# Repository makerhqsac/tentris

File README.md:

# tentris - Ten foot tall tetris game made from a boatload of neopixels

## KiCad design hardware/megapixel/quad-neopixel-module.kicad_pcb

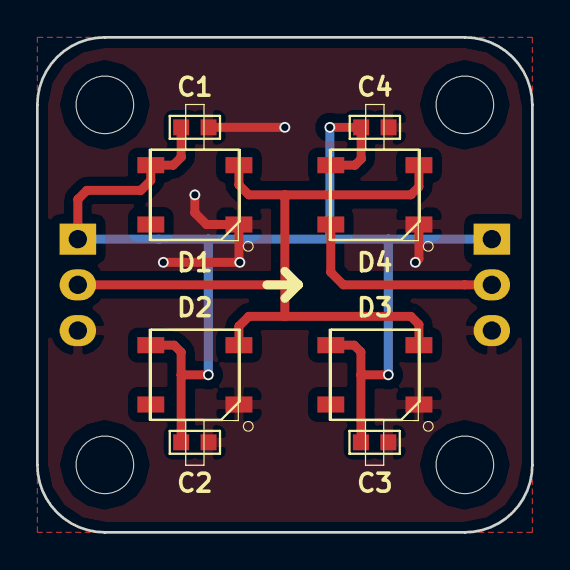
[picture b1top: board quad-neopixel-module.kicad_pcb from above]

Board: 2 copper layers, 27.5 x 27.5 mm, 10 parts (0 on the bottom side), 4 nets.

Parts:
C1, C2, C3, C4: CERAMIC-100NF-50V-10%-X7R_0603_; C0603
D1, D2, D3, D4: SMD-RGB-LED-4P; LED4-SMD-5050
P1, P2: CONN_01X03; Pin_Header_Straight_1x03

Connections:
DIN: D1.4, D2.4, D3.4, D4.4, P1.2
DOUT: D4.2, P2.2
GND: C1.2, C2.2, C3.2, C4.2, D1.3, D2.3, D3.3, D4.3, P1.3, P2.3
VCC: C1.1, C2.1, C3.1, C4.1, D1.1, D2.1, D3.1, D4.1, P1.1, P2.1

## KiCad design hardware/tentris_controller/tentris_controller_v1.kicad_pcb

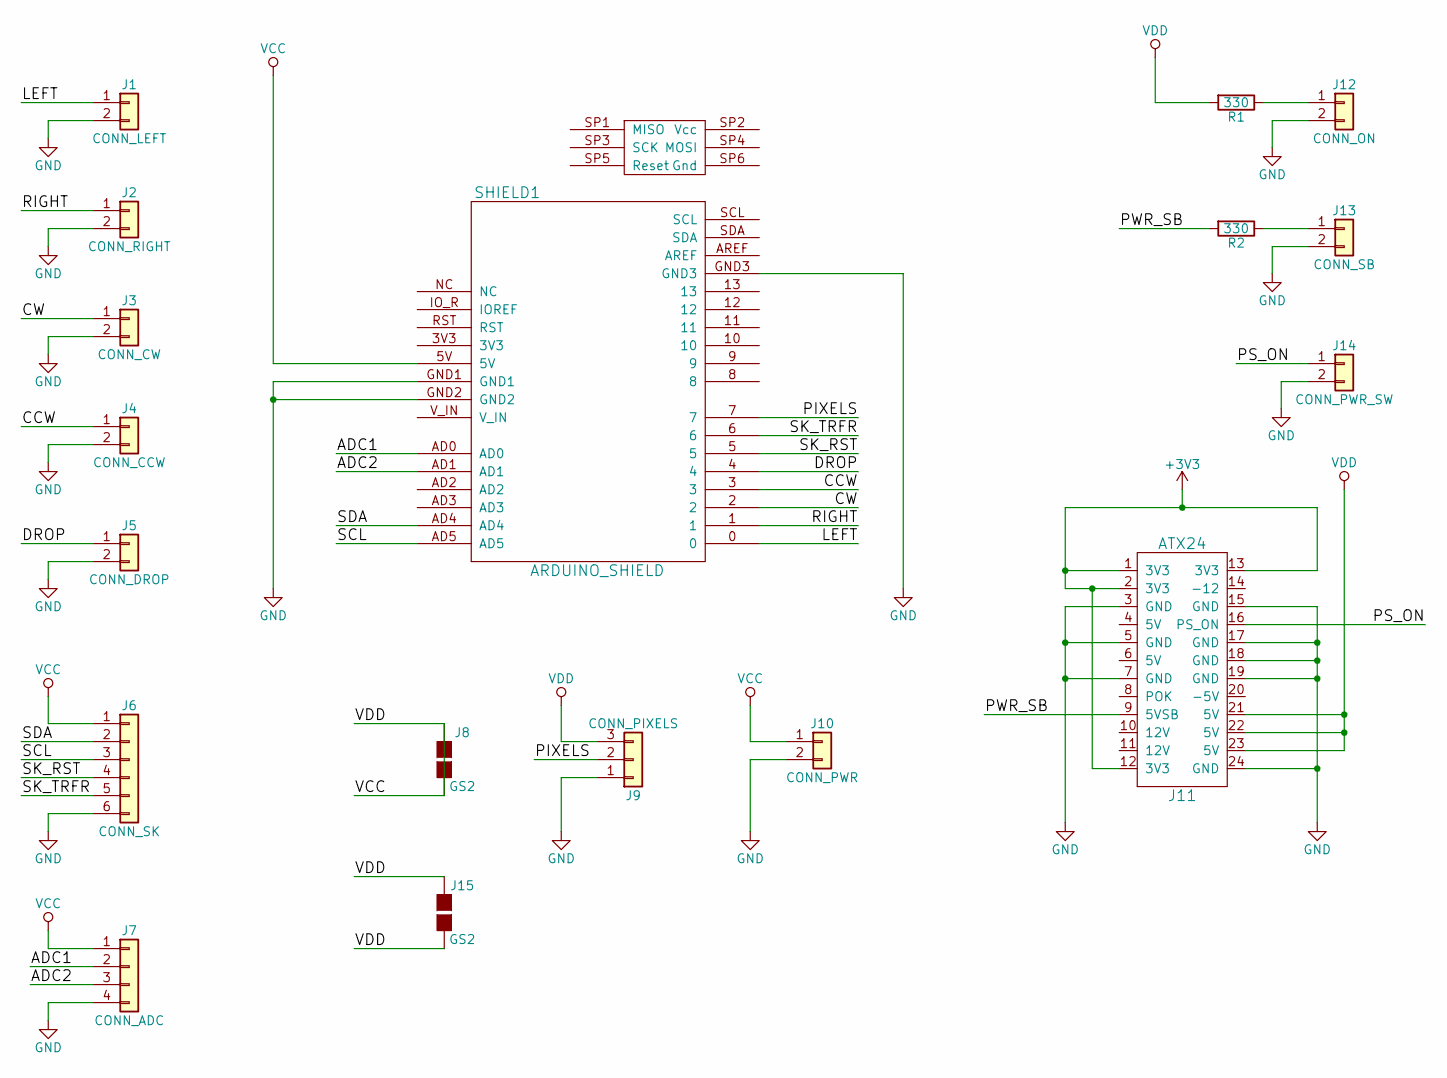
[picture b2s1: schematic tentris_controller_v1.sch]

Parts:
J1: CONN_LEFT; TerminalBlock_Pheonix_PT-3.5mm_2pol
J2: CONN_RIGHT; TerminalBlock_Pheonix_PT-3.5mm_2pol
J3: CONN_CW; TerminalBlock_Pheonix_PT-3.5mm_2pol
J4: CONN_CCW; TerminalBlock_Pheonix_PT-3.5mm_2pol
J5: CONN_DROP; TerminalBlock_Pheonix_PT-3.5mm_2pol
J6: CONN_SK; TerminalBlock_Pheonix_PT-3.5mm_6pol
J7: CONN_ADC; TerminalBlock_Pheonix_PT-3.5mm_4pol
J8: GS2
J9: CONN_PIXELS; TerminalBlock_Pheonix_PT-3.5mm_3pol
J10: CONN_PWR; TerminalBlock_Pheonix_PT-3.5mm_2pol
J11: ATX24; Molex_MiniFit-JR-5569-24A2_2x12x4.20mm_Angled
J12: CONN_ON; TerminalBlock_Pheonix_PT-3.5mm_2pol
J13: CONN_SB; TerminalBlock_Pheonix_PT-3.5mm_2pol
J14: CONN_PWR_SW; TerminalBlock_Pheonix_PT-3.5mm_2pol
J15: GS2; WireConnection_2.50mmDrill_LargePad
R1, R2: 330; R_Axial_DIN0204_L3.6mm_D1.6mm_P5.08mm_Horizontal
SHIELD1: ARDUINO_SHIELD

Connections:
+3V3: J11.1 (3V3), J11.2 (3V3), J11.12 (3V3), J11.13 (3V3)
/ADC1: J7.2, SHIELD1.AD0
/ADC2: J7.3, SHIELD1.AD1
/CCW: J4.1, SHIELD1.3
/CW: J3.1, SHIELD1.2
/DROP: J5.1, SHIELD1.4
/LEFT: J1.1, SHIELD1.0
/PIXELS: J9.2, SHIELD1.7
/PS_ON: J11.16 (PS_ON), J14.1
/PWR_SB: J11.9 (5VSB), R2.2
/RIGHT: J2.1, SHIELD1.1
/SCL: J6.3, SHIELD1.AD5
/SDA: J6.2, SHIELD1.AD4
/SK_RST: J6.4, SHIELD1.5
/SK_TRFR: J6.5, SHIELD1.6
GND: J1.2, J2.2, J3.2, J4.2, J5.2, J6.6, J7.4, J9.1, J10.2, J11.3 (GND), J11.5 (GND), J11.7 (GND), J11.15 (GND), J11.17 (GND), J11.18 (GND), J11.19 (GND), J11.24 (GND), J12.2, J13.2, J14.2, SHIELD1.GND1, SHIELD1.GND2, SHIELD1.GND3
unnamed: J12.1, R1.1
unnamed: J13.1, R2.1
VCC: J6.1, J7.1, J8.1 (G1), J8.2 (G2), J9.3, J10.1, J11.21 (5V), J11.22 (5V), J11.23 (5V), J15.1 (G1), J15.2 (G2), R1.2, SHIELD1.5V

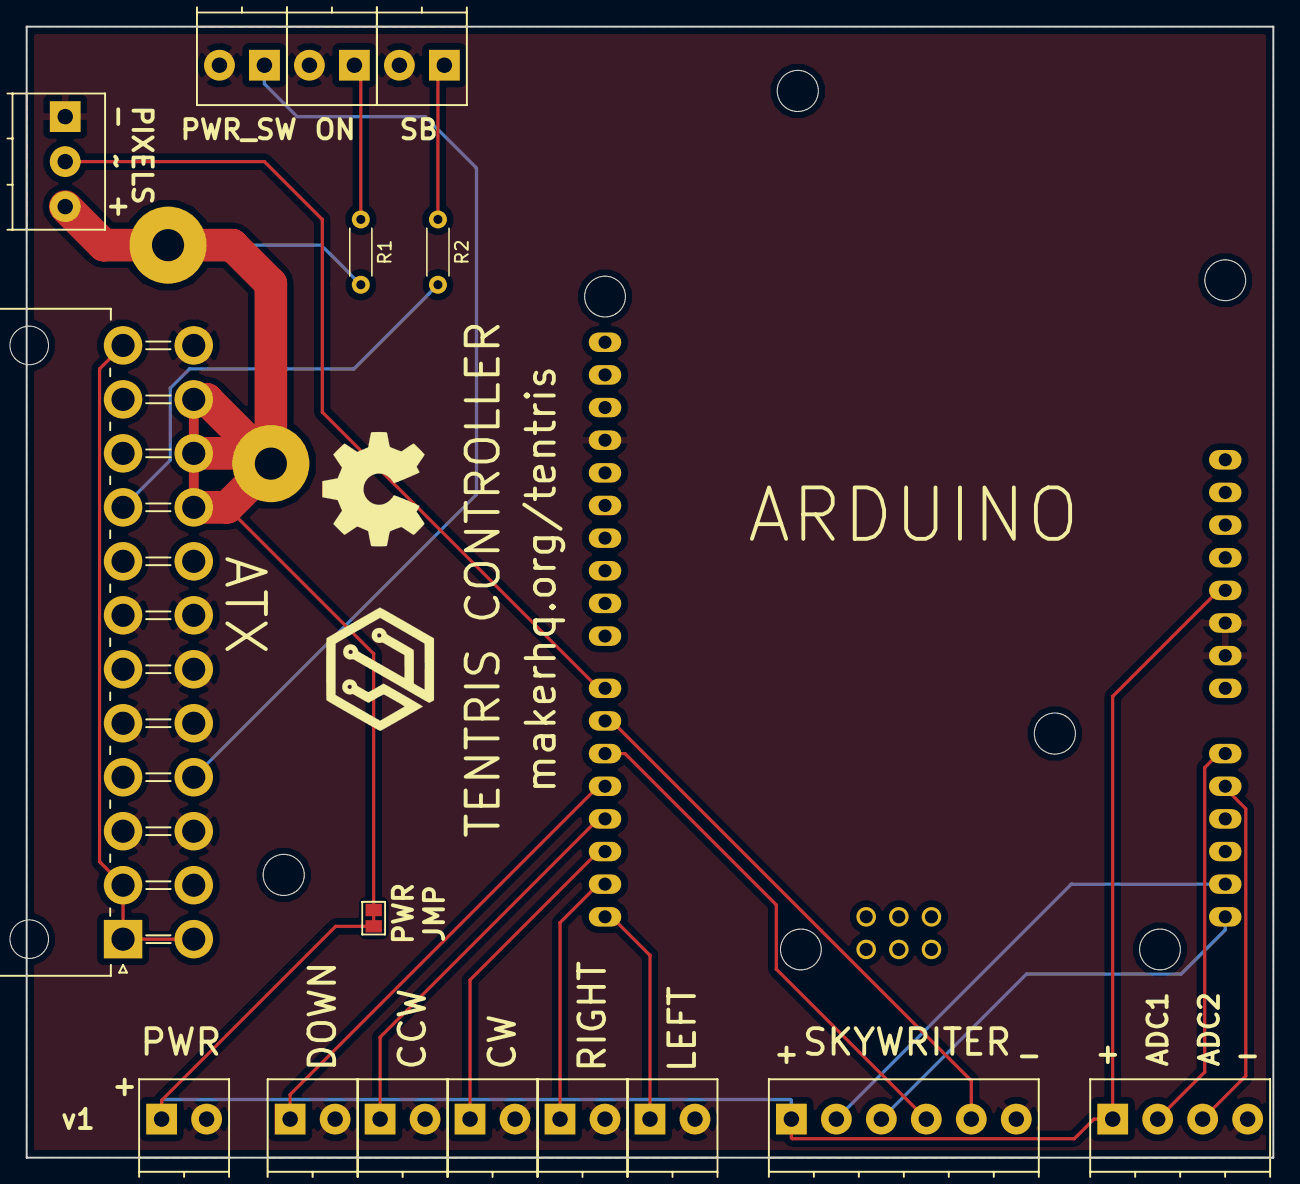
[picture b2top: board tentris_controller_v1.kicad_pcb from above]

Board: 2 copper layers, 97.0 x 88.0 mm, 18 parts (1 on the bottom side), 19 nets.

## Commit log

2017-09-18 Initial commit of reorg repo
2017-09-18 Add pixel_tester firmware
2017-09-18 Fix tester code
2017-09-18 Create Mechanical
    Files needed to laser cut the body.
2017-09-19 add mechanical
2017-09-19 add images
2017-09-20 Add megapixel kicad files
2017-09-21 Slowed down the box drops and added a speed increase as lines are cleared. Also, added wait animation.
2017-09-21 Slowed down the start even more. Changed anim delay into a configuration item. Now it starts off playable. Cleaned up some warnings.
2017-09-22 Added another animation. Cleaned up overflow causing random pixels. Pulled everything into the configuration. Added delay after clearing board after user starts game.
2017-09-25 Clear out EEPROM on first startup. Chances are at least. Saving high score. Added basic rain animation start. Added reverse rotation. Fixed bug with rotate dropping a row.
2017-09-26 Add skywriter support. make config match tentris controller board.
2017-09-29 fix inputs, add paint
2017-10-01 Fixed bugs in reverse rotate. Merged in Skywriter code. Added ability to gesture out of attract mode. Added bad hack to fix startup problem with Skywriter.
2017-10-07 Fixed rotate and merged sky and button
2017-10-12 rework clear and reset mechanisms
2017-10-13 Fixed memory issues
    Removed grid and used the NeoPixel library's internal storage for all lookups.
2017-10-14 Added scoring. Fixed overflow
2017-10-15 Collision delay
2017-10-15 hopefully fix skywriter connection issues
2017-10-15 support snake style pixel wiring
2017-10-16 allowed slide time adjusts down as score increases
2017-11-04 Added inverse
    Added the inverse direction for bottom-up wiriing like we have on the big board
2017-11-08 Added seven initial segment support
2017-12-23 Added new mapping for new layout
2017-12-23 Changed to matrix library
2018-04-26 Added support for serial score
    Added a serial score. Increments score every 200ms. Made score obnoxiously large with weird numbers.
2018-05-06 Modify tester to better work with gameboard
    Change output pin to 7
    Change number of pixels to 200
    Change brightness to 25% (64)
2018-05-10 Boundary issues
    Accidentally was stepping out of the array on the A0 and A1 buttons.
2018-05-17 new slide under code
2018-05-17 reset score to 0 on new game
